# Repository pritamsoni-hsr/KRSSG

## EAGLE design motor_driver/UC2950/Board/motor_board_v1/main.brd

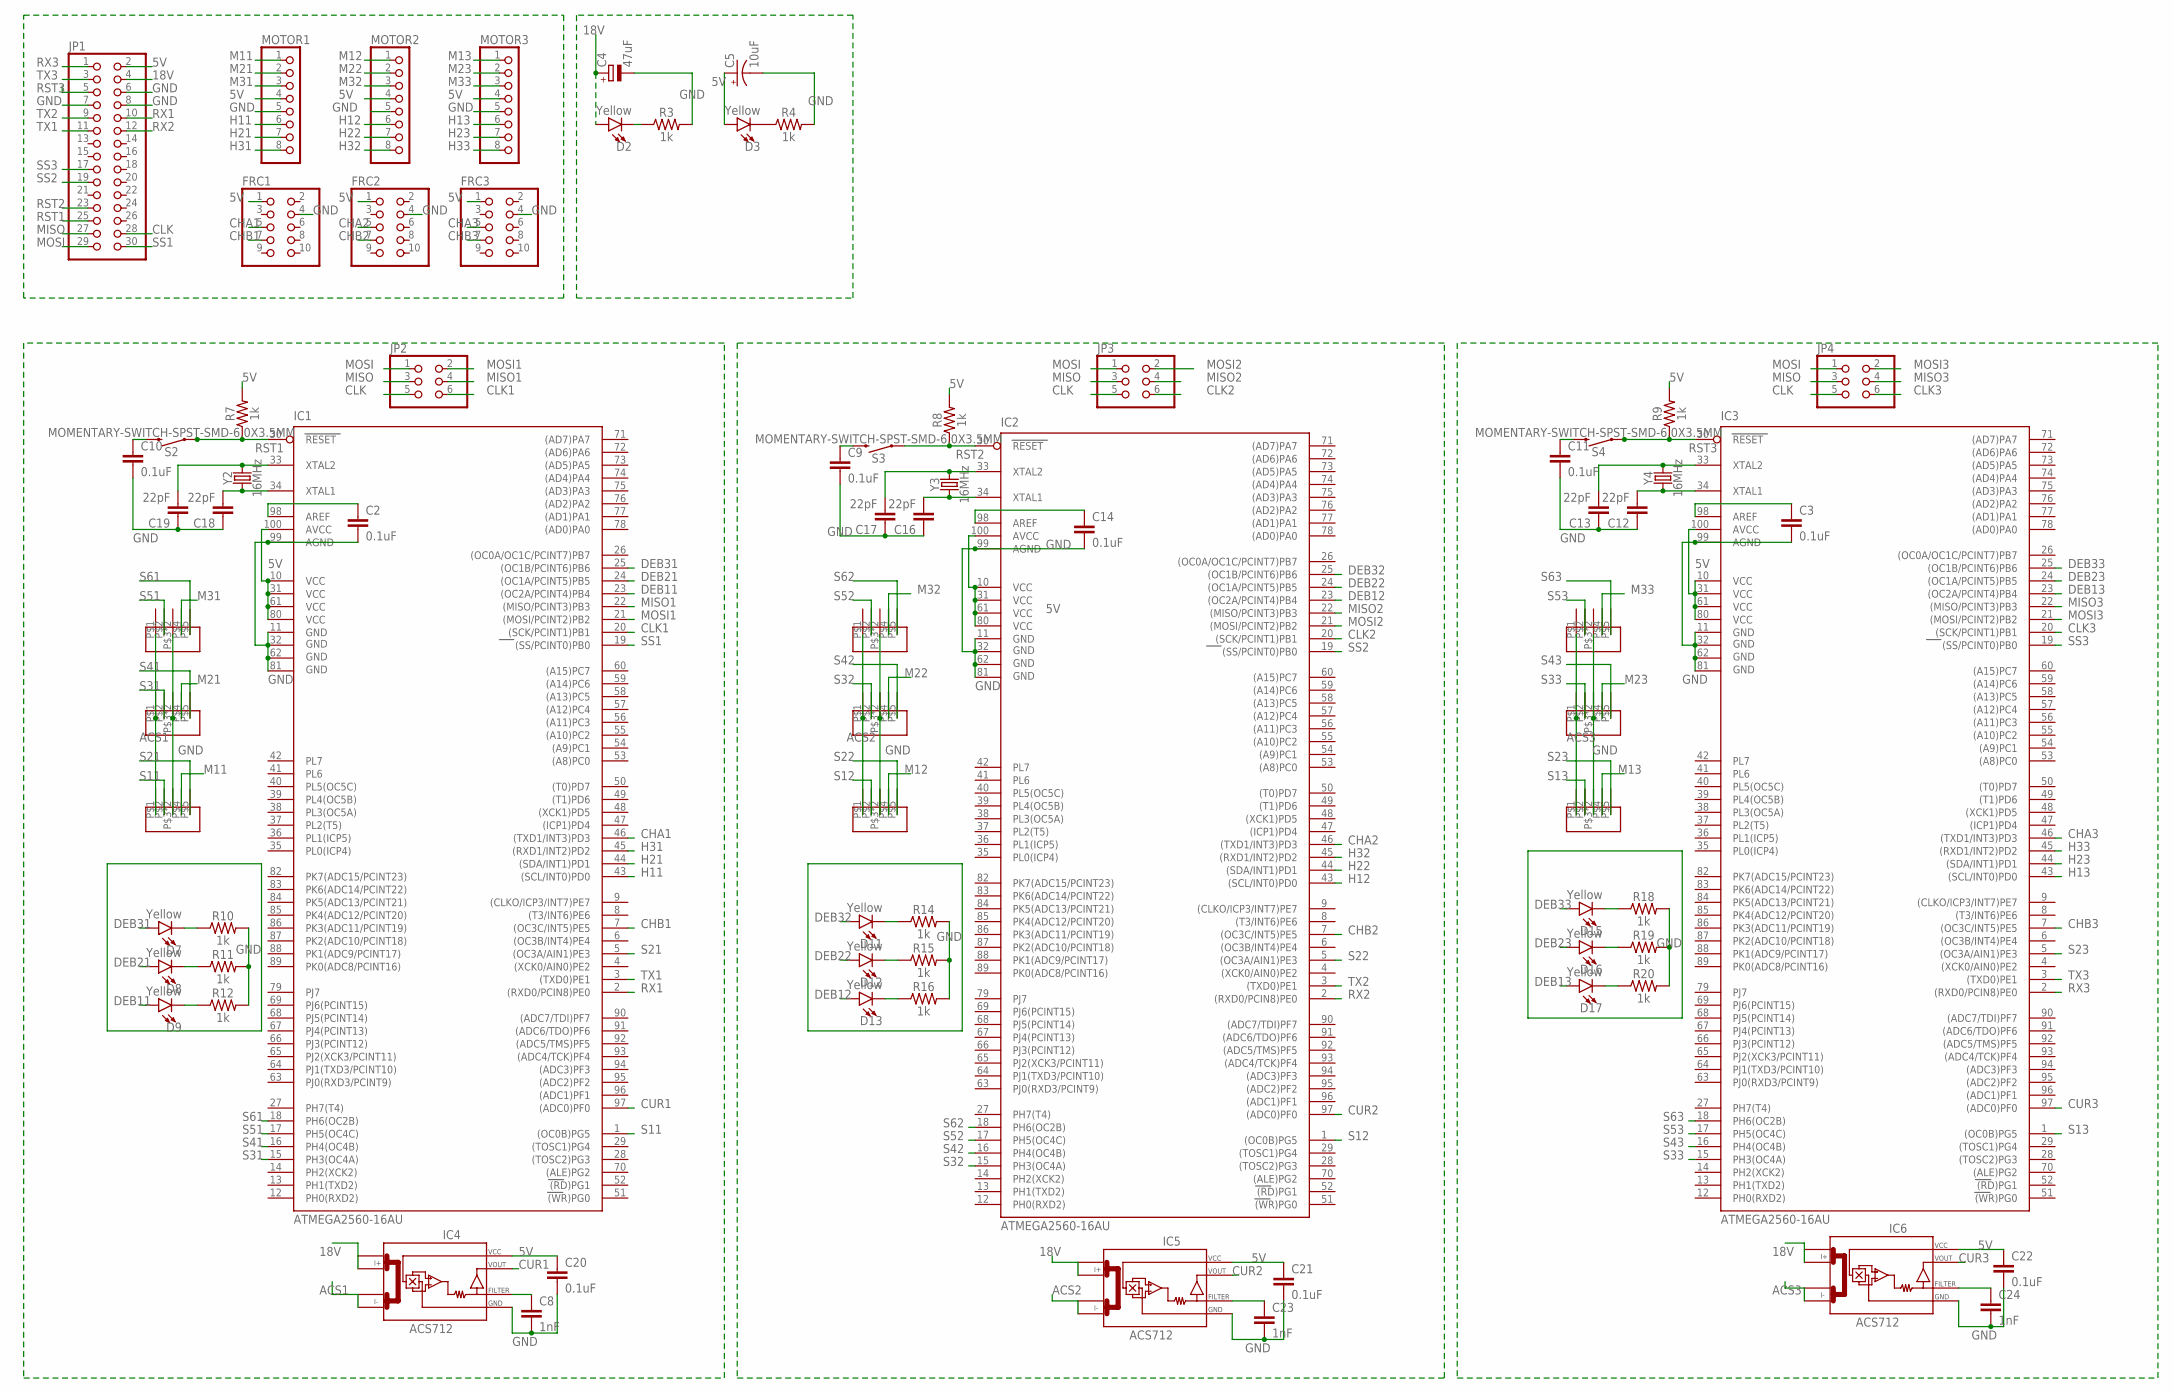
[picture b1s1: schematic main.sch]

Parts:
C2, C3, C9, C10, C11, C14, C20, C21, C22: 0.1uF; 0603
C4: 47uF; TAP5-60
C5: 10uF; 0603-POLAR
C8, C23, C24: 1nF; 0603
C12, C13, C16, C17, C18, C19: 22pF; 0603
D2, D3, D7, D8, D9, D11, D12, D13, D15, D16, D17: Yellow; LED-0603
FRC1, FRC2, FRC3: PINHD-2X5; 2X05
IC1, IC2, IC3: ATMEGA2560-16AU; TQFP100
IC4, IC5, IC6: ACS712; SO08
JP1: PINHD-2X15/90; 2X15/90
JP2, JP3, JP4: PINHD-2X3; 2X03
MIC1, MIC2, MIC3, MIC4, MIC5, MIC6, MIC7, MIC8, MIC9: UC2950
MOTOR1, MOTOR2, MOTOR3: PINHD-1X8; 1X08
R3, R4, R7, R8, R9, R10, R11, R12, R14, R15, R16, R18, R19, R20: 1k; 0603
S2, S3, S4: MOMENTARY-SWITCH-SPST-SMD-6.0X3.5MM; TACTILE_SWITCH_SMD_6.0X3.5MM
Y2, Y3, Y4: 16MHz; CRYSTAL-SMD-5X3.2-4PAD

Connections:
5V: C5.+, C20.1, C21.1, C22.1, D3.A, FRC1.1, FRC2.1, FRC3.1, IC1.10 (VCC), IC1.31 (VCC1), IC1.61 (VCC2), IC1.80 (VCC3), IC1.100 (AVCC), IC2.10 (VCC), IC2.31 (VCC1), IC2.61 (VCC2), IC2.80 (VCC3), IC2.100 (AVCC), IC3.10 (VCC), IC3.31 (VCC1), IC3.61 (VCC2), IC3.80 (VCC3), IC3.100 (AVCC), IC4.8 (VCC), IC5.8 (VCC), IC6.8 (VCC), JP1.2, MOTOR1.4, MOTOR2.4, MOTOR3.4, R7.2, R8.2, R9.2
18V: C4.+, D2.A, IC4.1 (I+_0), IC5.1 (I+_0), IC6.1 (I+_0), JP1.4
ACS1: IC4.3 (I-_0), MIC1.P$1, MIC2.P$1, MIC3.P$1
ACS2: IC5.3 (I-_0), MIC4.P$1, MIC5.P$1, MIC6.P$1
ACS3: IC6.3 (I-_0), MIC7.P$1, MIC8.P$1, MIC9.P$1
CHA1: FRC1.5, IC1.46 ((TXD1/INT3)PD3)
CHA2: FRC2.5, IC2.46 ((TXD1/INT3)PD3)
CHA3: FRC3.5, IC3.46 ((TXD1/INT3)PD3)
CHB1: FRC1.7, IC1.7 ((OC3C/INT5)PE5)
CHB2: FRC2.7, IC2.7 ((OC3C/INT5)PE5)
CHB3: FRC3.7, IC3.7 ((OC3C/INT5)PE5)
CLK: JP1.28, JP2.5, JP3.5, JP4.5
CLK1: IC1.20 ((SCK/PCINT1)PB1), JP2.6
CLK2: IC2.20 ((SCK/PCINT1)PB1), JP3.6
CLK3: IC3.20 ((SCK/PCINT1)PB1), JP4.6
CUR1: IC1.97 ((ADC0)PF0), IC4.7 (VOUT)
CUR2: IC2.97 ((ADC0)PF0), IC5.7 (VOUT)
CUR3: IC3.97 ((ADC0)PF0), IC6.7 (VOUT)
DEB11: D9.A, IC1.23 ((OC2A/PCINT4)PB4)
DEB12: D13.A, IC2.23 ((OC2A/PCINT4)PB4)
DEB13: D17.A, IC3.23 ((OC2A/PCINT4)PB4)
DEB21: D8.A, IC1.24 ((OC1A/PCINT5)PB5)
DEB22: D12.A, IC2.24 ((OC1A/PCINT5)PB5)
DEB23: D16.A, IC3.24 ((OC1A/PCINT5)PB5)
DEB31: D7.A, IC1.25 ((OC1B/PCINT6)PB6)
DEB32: D11.A, IC2.25 ((OC1B/PCINT6)PB6)
DEB33: D15.A, IC3.25 ((OC1B/PCINT6)PB6)
GND: C2.2, C3.2, C4.-, C5.-, C8.2, C9.2, C10.2, C11.2, C12.1, C13.1, C14.2, C16.1, C17.1, C18.1, C19.1, C20.2, C21.2, C22.2, C23.2, C24.2, FRC1.4, FRC2.4, FRC3.4, IC1.11 (GND), IC1.32 (GND1), IC1.62 (GND2), IC1.81 (GND3), IC1.99 (AGND), IC2.11 (GND), IC2.32 (GND1), IC2.62 (GND2), IC2.81 (GND3), IC2.99 (AGND), IC3.11 (GND), IC3.32 (GND1), IC3.62 (GND2), IC3.81 (GND3), IC3.99 (AGND), IC4.5 (GND), IC5.5 (GND), IC6.5 (GND), JP1.6, JP1.7, JP1.8, MIC1.P$3, MIC1.P$6, MIC2.P$3, MIC2.P$6, MIC3.P$3, MIC3.P$6, MIC4.P$3, MIC4.P$6, MIC5.P$3, MIC5.P$6, MIC6.P$3, MIC6.P$6, MIC7.P$3, MIC7.P$6, MIC8.P$3, MIC8.P$6, MIC9.P$3, MIC9.P$6, MOTOR1.5, MOTOR2.5, MOTOR3.5, R3.2, R4.2, R10.2, R11.2, R12.2, R14.2, R15.2, R16.2, R18.2, R19.2, R20.2
H11: IC1.43 ((SCL/INT0)PD0), MOTOR1.6
H12: IC2.43 ((SCL/INT0)PD0), MOTOR2.6
H13: IC3.43 ((SCL/INT0)PD0), MOTOR3.6
H21: IC1.44 ((SDA/INT1)PD1), MOTOR1.7
H22: IC2.44 ((SDA/INT1)PD1), MOTOR2.7
H23: IC3.44 ((SDA/INT1)PD1), MOTOR3.7
H31: IC1.45 ((RXD1/INT2)PD2), MOTOR1.8
H32: IC2.45 ((RXD1/INT2)PD2), MOTOR2.8
H33: IC3.45 ((RXD1/INT2)PD2), MOTOR3.8
M11: MIC3.P$4, MOTOR1.1
M12: MIC6.P$4, MOTOR2.1
M13: MIC7.P$4, MOTOR3.1
M21: MIC2.P$4, MOTOR1.2
M22: MIC5.P$4, MOTOR2.2
M23: MIC8.P$4, MOTOR3.2
M31: MIC1.P$4, MOTOR1.3
M32: MIC4.P$4, MOTOR2.3
M33: MIC9.P$4, MOTOR3.3
MISO: JP1.27, JP2.3, JP3.3, JP4.3
MISO1: IC1.22 ((MISO/PCINT3)PB3), JP2.4
MISO2: IC2.22 ((MISO/PCINT3)PB3), JP3.4
MISO3: IC3.22 ((MISO/PCINT3)PB3), JP4.4
MOSI: JP1.29, JP2.1, JP3.1, JP4.1
MOSI1: IC1.21 ((MOSI/PCINT2)PB2), JP2.2
MOSI2: IC2.21 ((MOSI/PCINT2)PB2), JP3.2
MOSI3: IC3.21 ((MOSI/PCINT2)PB2), JP4.2
unnamed: D2.C, R3.1
unnamed: C2.1, IC1.98 (AREF)
unnamed: D3.C, R4.1
unnamed: C10.1, S2.2
unnamed: C3.1, IC3.98 (AREF)
unnamed: C11.1, S4.2
unnamed: C14.1, IC2.98 (AREF)
unnamed: C9.1, S3.2
unnamed: C19.2, IC1.33 (XTAL2), Y2.3 (2)
unnamed: C17.2, IC2.33 (XTAL2), Y3.3 (2)
unnamed: C16.2, IC2.34 (XTAL1), Y3.1
unnamed: C18.2, IC1.34 (XTAL1), Y2.1
unnamed: C13.2, IC3.33 (XTAL2), Y4.3 (2)
unnamed: C12.2, IC3.34 (XTAL1), Y4.1
unnamed: C8.1, IC4.6 (FILTER)
unnamed: C23.1, IC5.6 (FILTER)
unnamed: C24.1, IC6.6 (FILTER)
unnamed: D7.C, R10.1
unnamed: D8.C, R11.1
unnamed: D9.C, R12.1
unnamed: D11.C, R14.1
unnamed: D12.C, R15.1
unnamed: D13.C, R16.1
unnamed: D15.C, R18.1
unnamed: D16.C, R19.1
unnamed: D17.C, R20.1
RST1: IC1.30 (RESET), JP1.25, R7.1, S2.1
RST2: IC2.30 (RESET), JP1.23, R8.1, S3.1
RST3: IC3.30 (RESET), JP1.5, R9.1, S4.1
RX1: IC1.2 ((RXD0/PCIN8)PE0), JP1.10
RX2: IC2.2 ((RXD0/PCIN8)PE0), JP1.12
RX3: IC3.2 ((RXD0/PCIN8)PE0), JP1.1
S11: IC1.1 ((OC0B)PG5), MIC3.P$2
S12: IC2.1 ((OC0B)PG5), MIC6.P$2
S13: IC3.1 ((OC0B)PG5), MIC7.P$2
S21: IC1.5 ((OC3A/AIN1)PE3), MIC3.P$5
S22: IC2.5 ((OC3A/AIN1)PE3), MIC6.P$5
S23: IC3.5 ((OC3A/AIN1)PE3), MIC7.P$5
S31: IC1.15 (PH3(OC4A)), MIC2.P$2
S32: IC2.15 (PH3(OC4A)), MIC5.P$2
S33: IC3.15 (PH3(OC4A)), MIC8.P$2
S41: IC1.16 (PH4(OC4B)), MIC2.P$5
S42: IC2.16 (PH4(OC4B)), MIC5.P$5
S43: IC3.16 (PH4(OC4B)), MIC8.P$5
S51: IC1.17 (PH5(OC4C)), MIC1.P$2
S52: IC2.17 (PH5(OC4C)), MIC4.P$2
S53: IC3.17 (PH5(OC4C)), MIC9.P$2
S61: IC1.18 (PH6(OC2B)), MIC1.P$5
S62: IC2.18 (PH6(OC2B)), MIC4.P$5
S63: IC3.18 (PH6(OC2B)), MIC9.P$5
SS1: IC1.19 ((SS/PCINT0)PB0), JP1.30
SS2: IC2.19 ((SS/PCINT0)PB0), JP1.19
SS3: IC3.19 ((SS/PCINT0)PB0), JP1.17
TX1: IC1.3 ((TXD0)PE1), JP1.11
TX2: IC2.3 ((TXD0)PE1), JP1.9
TX3: IC3.3 ((TXD0)PE1), JP1.3

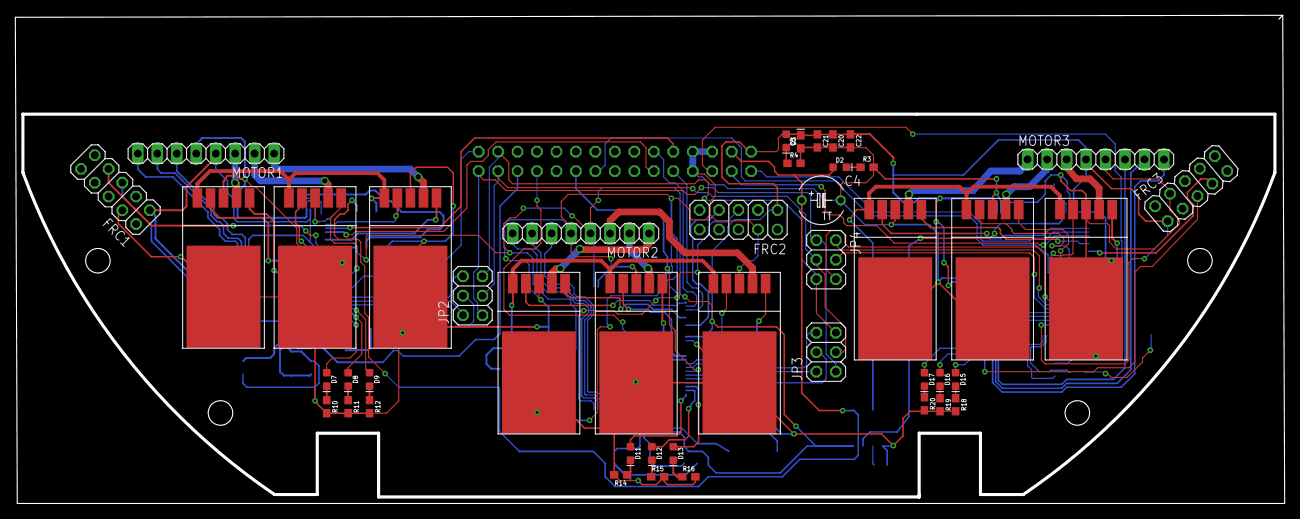
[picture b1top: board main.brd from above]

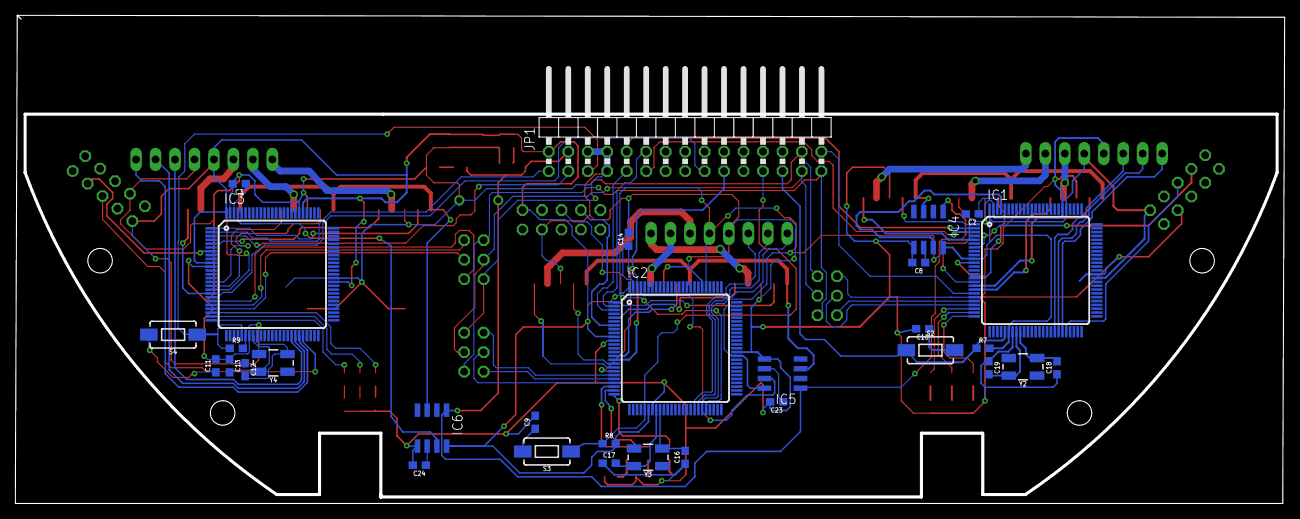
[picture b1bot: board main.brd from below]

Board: 2 copper layers, 165.2 x 63.3 mm, 76 parts (31 on the bottom side), 110 nets.

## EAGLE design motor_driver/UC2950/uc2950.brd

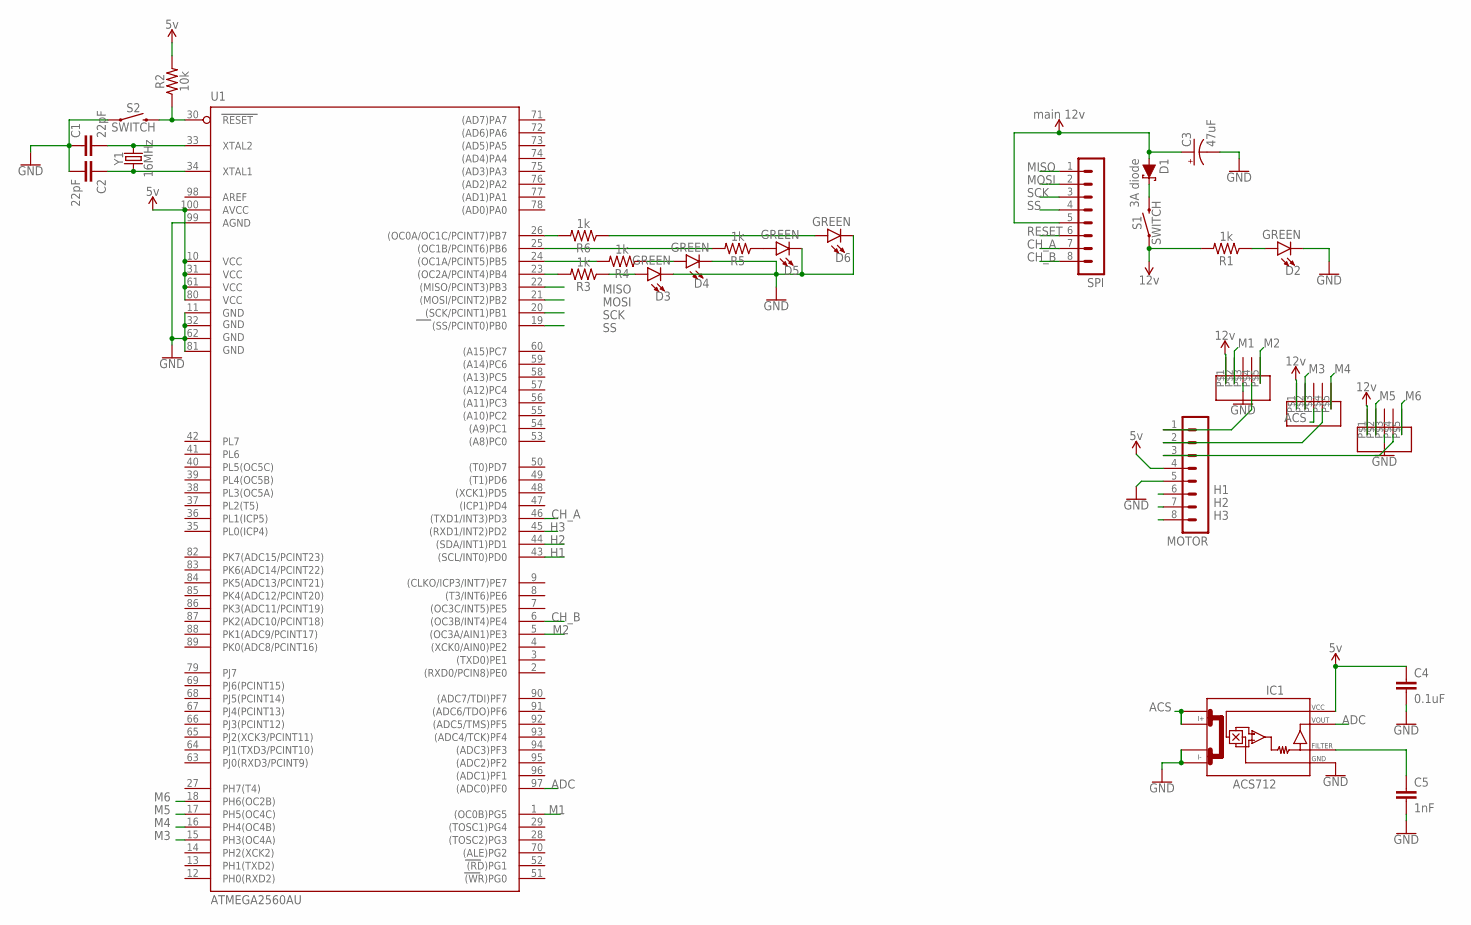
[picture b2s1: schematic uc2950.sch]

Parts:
C1, C2: 22pF; 0603
C3: 47uF; EIA3528
C4: 0.1uF; 0603
C5: 1nF; 0603
D1: 3A diode; SMA-DIODE
D2, D3, D4, D5, D6: GREEN; LED-0603
IC1: ACS712; SO08
M1: M1; UC2950
M2: M2; UC2950
M3: M3; UC2950
MOTOR: MA08-1
R1, R3, R4, R5, R6: 1k; 0603
R2: 10k; 0603
S1, S2: SWITCH; TACTILE_SWITCH_SMD_4.6X2.8MM
SPI: MA08-1
U1: ATMEGA2560AU; TQFP100
Y1: 16MHz; CRYSTAL-SMD-5X3.2-4PAD

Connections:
ACS: IC1.1 (I+_0), IC1.2 (I+_1), M2.P$3
ADC: IC1.7 (VOUT), U1.97 ((ADC0)PF0)
CH_A: SPI.7, U1.46 ((TXD1/INT3)PD3)
CH_B: SPI.8, U1.6 ((OC3B/INT4)PE4)
GND: C1.1, C2.2, C3.C (-), C4.2, C5.2, D2.C, D3.C, D4.C, D5.C, D6.C, IC1.3 (I-_0), IC1.4 (I-_1), IC1.5 (GND), M1.P$3, M3.P$3, MOTOR.5, S2.1, S2.2 (1), U1.11 (GND), U1.32 (GND1), U1.62 (GND2), U1.81 (GND3), U1.99 (AGND)
H1: MOTOR.6, U1.43 ((SCL/INT0)PD0)
H2: MOTOR.7, U1.44 ((SDA/INT1)PD1)
H3: MOTOR.8, U1.45 ((RXD1/INT2)PD2)
M1: M1.P$2, U1.1 ((OC0B)PG5)
M2: M1.P$5, U1.5 ((OC3A/AIN1)PE3)
M3: M2.P$2, U1.15 (PH3(OC4A))
M4: M2.P$5, U1.16 (PH4(OC4B))
M5: M3.P$2, U1.17 (PH5(OC4C))
M6: M3.P$5, U1.18 (PH6(OC2B))
MISO: SPI.1, U1.22 ((MISO/PCINT3)PB3)
MOSI: SPI.2, U1.21 ((MOSI/PCINT2)PB2)
unnamed: D1.C, S1.3 (2), S1.4 (2)
unnamed: D2.A, R1.1
unnamed: M1.P$4, MOTOR.1
unnamed: M3.P$4, MOTOR.3
unnamed: M2.P$4, MOTOR.2
unnamed: C5.1, IC1.6 (FILTER)
unnamed: C1.2, U1.33 (XTAL2), Y1.3 (2)
unnamed: C2.1, U1.34 (XTAL1), Y1.1
unnamed: R4.2, U1.24 ((OC1A/PCINT5)PB5)
unnamed: D3.A, R3.1
unnamed: D4.A, R4.1
unnamed: D5.A, R5.1
unnamed: D6.A, R6.1
unnamed: R3.2, U1.23 ((OC2A/PCINT4)PB4)
unnamed: R5.2, U1.25 ((OC1B/PCINT6)PB6)
unnamed: R6.2, U1.26 ((OC0A/OC1C/PCINT7)PB7)
RESET: R2.1, S2.3 (2), S2.4 (2), SPI.6, U1.30 (RESET)
SCK: SPI.3, U1.20 ((SCK/PCINT1)PB1)
SS: SPI.4, U1.19 ((SS/PCINT0)PB0)
VCCIO: C4.1, IC1.8 (VCC), MOTOR.4, R2.2, U1.10 (VCC), U1.31 (VCC1), U1.61 (VCC2), U1.80 (VCC3), U1.100 (AVCC)
VCC_1: C3.A (+), D1.A, SPI.5
VCC_2: M1.P$1, M2.P$1, M3.P$1, R1.2, S1.1, S1.2 (1)

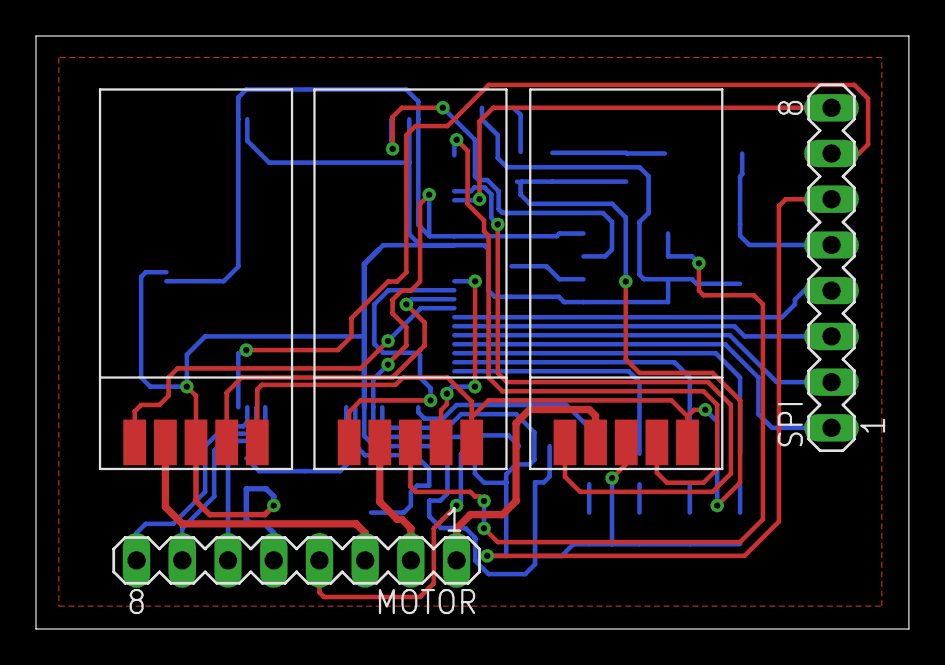
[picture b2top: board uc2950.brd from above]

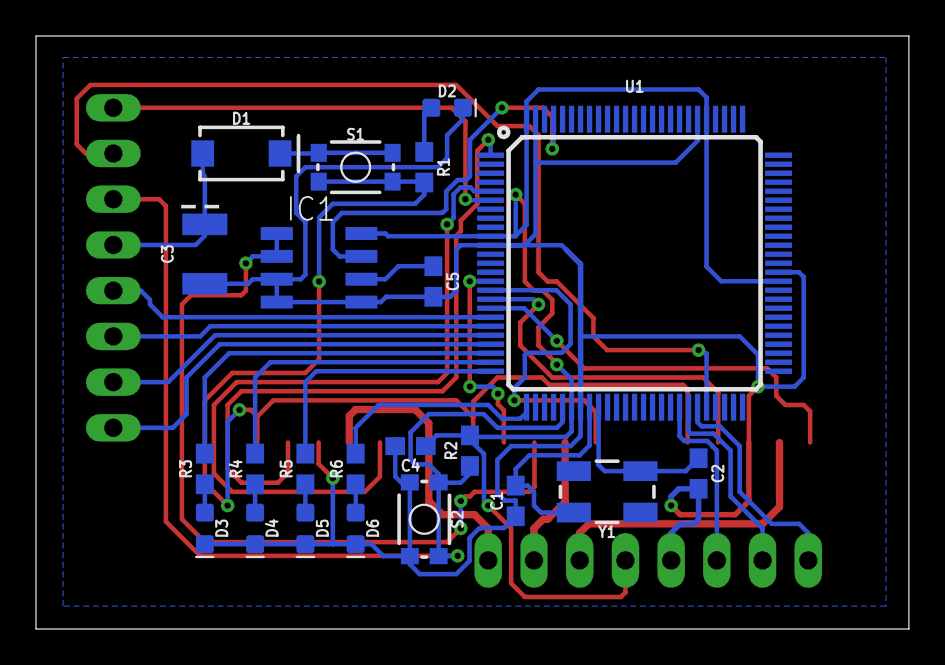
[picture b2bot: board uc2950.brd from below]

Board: 2 copper layers, 48.5 x 32.9 mm, 27 parts (22 on the bottom side), 38 nets.

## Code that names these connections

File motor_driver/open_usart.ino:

#include <avr/io.h>
#include <avr/interrupt.h>

//pins
int S1=4; //pg5
int S2=5; //pe3
int S3=6; //ph3
int S4=7; //ph4
int S5=8; //ph5
int S6=9; //ph6

int H1=21;  //pd0
int H2=20;  //pd1
int H3=19;  //pd2

int D1=10; //PB3
int D2=11; //PB5
int D3=12; //PB6
uint16_t data=0;
//variables
int pwm_value=0;
bool drxn=0;

void Stop(){
  analogWrite(S1,255);
  analogWrite(S3,255);
  analogWrite(S5,255);
  analogWrite(S2,0);
  analogWrite(S4,0);
  analogWrite(S6,0);
}
// Commutation table
volatile int HallValue(){
  return((digitalRead(H1))+(digitalRead(H2)*2)+(digitalRead(H3)*4));	//Bases are 1,2,4.
}
void Check_PWM_CW(volatile int HallValue){
  switch(HallValue){
   case 0: {
	Stop();
	break;
}
   case 3: {                                      //0. +. -
	analogWrite(S1,0);
	analogWrite(S2,255);
	analogWrite(S3,pwm_value);
	analogWrite(S4,0);
	analogWrite(S5,0);
	analogWrite(S6,0);
	break;
   }
   case 2: {                                      //-. +. 0
	analogWrite(S1,0);
	analogWrite(S2,0);
	analogWrite(S3,pwm_value);
	analogWrite(S4,0);
	analogWrite(S5,0);
	analogWrite(S6,255);
	break;
}
   case 6: {                                      //-. 0. +
	analogWrite(S1,0);
	analogWrite(S2,0);
	analogWrite(S3,0);
	analogWrite(S4,255);
	analogWrite(S5,pwm_value);
	analogWrite(S6,0);
	break;
    }
   case 4: {                                      //0. -. +
	analogWrite(S1,0);
	analogWrite(S2,255);
	analogWrite(S3,0);
	analogWrite(S4,0);
	analogWrite(S5,pwm_value);
	analogWrite(S6,0);
break;
   }
   case 5: {                                      //+. -. 0
	analogWrite(S1,pwm_value);
	analogWrite(S2,0);
	analogWrite(S3,0);
	analogWrite(S4,0);
	analogWrite(S5,0);
	analogWrite(S6,255);
	break;
    }
  case 1: {                                       //+. 0. -
	analogWrite(S1,pwm_value);
	analogWrite(S2,0);
	analogWrite(S3,0);
	analogWrite(S4,255);
	analogWrite(S5,0);
	analogWrite(S6,0);
	break;
   }
  case 7:{
   Stop();
   break;
  }
 }
}
void Check_PWM_CCW(volatile int HallValue){
  switch(HallValue){
   case 0: {
     Stop();
     break;
   }
   case 3: {
     analogWrite(S1,0);
     analogWrite(S2,255);
     analogWrite(S3,0);
     analogWrite(S4,0);
     analogWrite(S5,pwm_value);
     analogWrite(S6,0);
     break;
   }
   case 2: {
     analogWrite(S1,pwm_value);
     analogWrite(S2,0);
     analogWrite(S3,0);
     analogWrite(S4,0);
     analogWrite(S5,0);
     analogWrite(S6,255);
     break;
    }
   case 6: {
     analogWrite(S1,pwm_value);
     analogWrite(S2,0);
     analogWrite(S3,0);
     analogWrite(S4,255);
     analogWrite(S5,0);
     analogWrite(S6,0);
     break;
    }
   case 4: {
     analogWrite(S1,0);
     analogWrite(S2,255);
     analogWrite(S3,pwm_value);
     analogWrite(S4,0);
     analogWrite(S5,0);
     analogWrite(S6,0);
     break;
   }
   case 5: {
     analogWrite(S1,0);
     analogWrite(S2,0);
     analogWrite(S3,pwm_value);
     analogWrite(S4,0);
     analogWrite(S5,0);
     analogWrite(S6,255);
     break;
    }
  case 1: {
     analogWrite(S1,0);
     analogWrite(S2,0);
     analogWrite(S3,0);
     analogWrite(S4,255);
     analogWrite(S5,pwm_value);
     analogWrite(S6,0);
     break;
   }
  case 7:
  {
   Stop();
   break;
  }
 }
}
void Init_Pins(){
  pinMode(S1,OUTPUT);
  pinMode(S2,OUTPUT);
  pinMode(S3,OUTPUT);
  pinMode(S4,OUTPUT);
  pinMode(S5,OUTPUT);
  pinMode(S6,OUTPUT);
  pinMode(H1,INPUT);
  pinMode(H2,INPUT);
  pinMode(H3,INPUT);
  pinMode(D1,OUTPUT);
  pinMode(D2,OUTPUT);
  pinMode(D3,OUTPUT);
  pinMode(18,INPUT);
  pinMode(17,INPUT);
}
void Init_Interrupt(){
  sei();
  TCCR1B|=(1<<CS10)|(0<<CS11)|(0<<CS12);
  TCCR2B|=(1<<CS20)|(0<<CS21)|(0<<CS22);
  TCCR3B|=(1<<CS30)|(0<<CS31)|(0<<CS32);
  EIMSK=(1<<INT0)|(1<<INT1)|(1<<INT2)|(1<<INT3);
  EICRA=(1<<ISC00)|(1<<ISC10)|(1<<ISC20)|(1<<ISC30);
}
ISR(INT0_vect){
  if (drxn == 0)
    Check_PWM_CW(HallValue());
  else if (drxn == 1)
    Check_PWM_CCW(HallValue());
}
ISR(INT1_vect){
  if (drxn == 0)
    Check_PWM_CW(HallValue());
  else if (drxn == 1)
    Check_PWM_CCW(HallValue());
}
ISR(INT2_vect){
  if (drxn == 0)
    Check_PWM_CW(HallValue());
  else if (drxn == 1)
    Check_PWM_CCW(HallValue());
}
void receiveData(){
  if (Serial.available()>0){
    data = Serial.read(); //stores data in bytes 
    pwm_value=data%127;
    drxn=data/127;
  }
}
int main(){
	Serial.begin(115200);
	Init_Pins();
  Init_Interrupt();
  
	while(1){
	receiveData();
	}
}

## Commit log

2017-12-15 Repo Initialised
2017-12-15 All MCU/motor driver codes
2017-12-16 lm5107 eagle file added
2018-02-22 UC2950 Eagle Files
2018-04-01 bidirectional rx speed
2018-04-01 stm tx code for speed
2018-04-01 MotorDriverBoard eaglefiles
2018-05-09 open loop with usart for final circuit
2018-05-13 added 12V supply
2018-05-20 resolved previous errors
2018-05-21 header position mod
2018-05-22 aditya's stm code
    IRS4427

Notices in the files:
parts and their libraries:
SparkFun-Capacitors: Licensing: Creative Commons ShareAlike 4.0 International - https://creativecommons.org/licenses/by-sa/4.0
